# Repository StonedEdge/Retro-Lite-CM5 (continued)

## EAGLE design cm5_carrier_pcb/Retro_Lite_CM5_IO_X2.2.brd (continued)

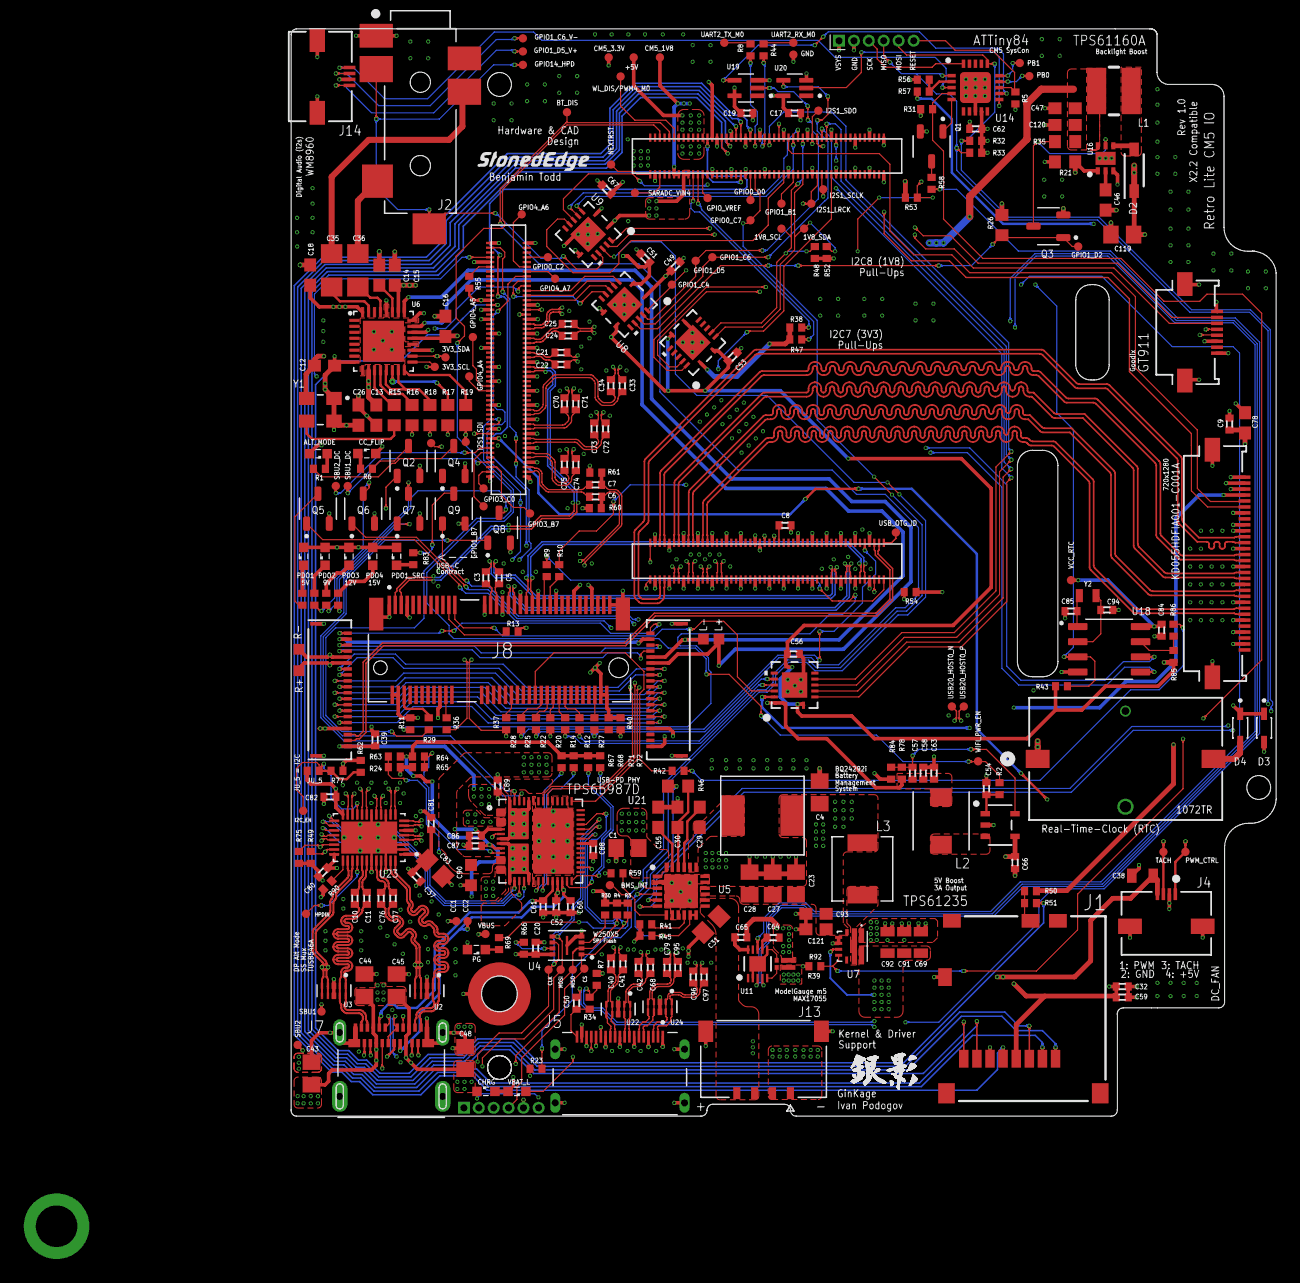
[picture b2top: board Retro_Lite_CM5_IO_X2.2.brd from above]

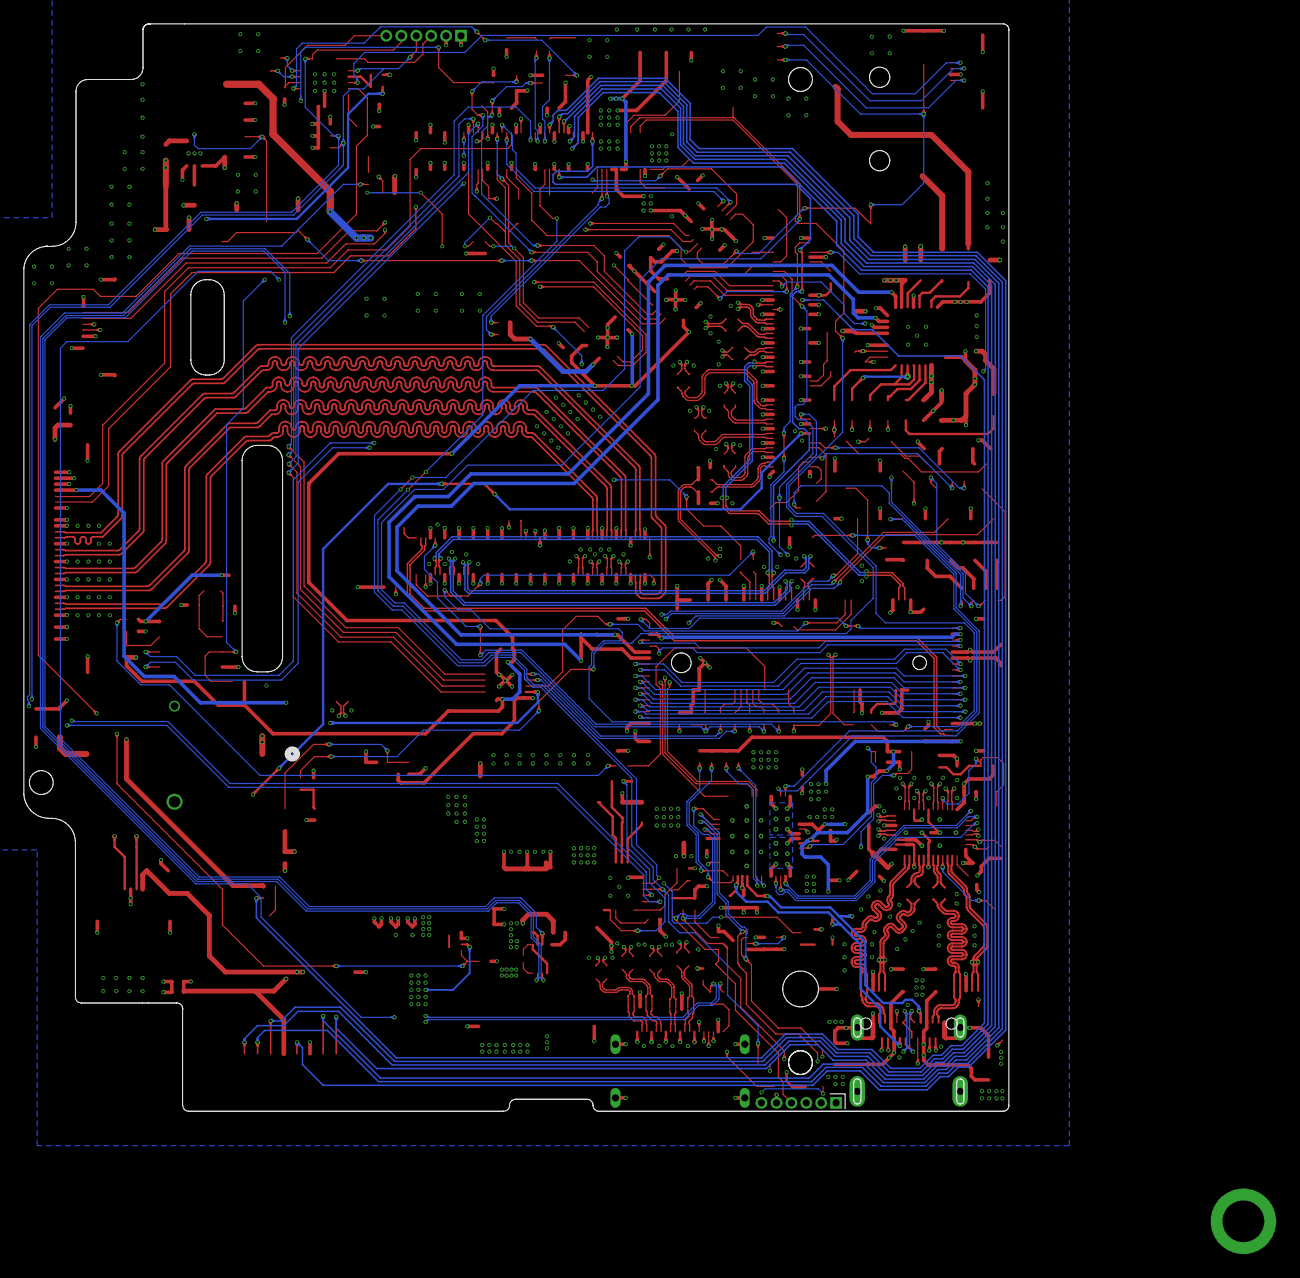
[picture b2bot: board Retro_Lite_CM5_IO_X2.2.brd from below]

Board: 6 copper layers, 82.7 x 91.3 mm, 318 parts (2 on the bottom side), 286 nets.

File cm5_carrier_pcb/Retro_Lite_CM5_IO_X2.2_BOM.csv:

Qty,Value,Device,Package,Parts,Description
6,N/A,LEDSML0603,SML0603,"PDO1, PDO1_SRC, PDO2, PDO3, PDO4, SSMX_DP_ACTIVE, SSMX_FLIP_ACTIVE",BLUE_LED_GENERIC
1,N/A,LEDSML0603,SML0603,CHRG,WHITE_LED_GENERIC
1,N/A,LEDSML0603,SML0603,VBAT_L,RED_LED_GENERIC
5,0R,R-EU_R0402,R0402,"JU_5, R13, R34, R36, R42",Resistor
1,0.047µF,C-EUC0603,C0603,C29,Capacitor
1,0.1uF,C-EUC0402,C0402,C20,Capacitor
6,0.1uF,C-EUC0402-YVELTAL,C0402,"C17, C19, C39, C54, C62, C65",Capacitor
4,0.1uF,C-EUC0603,C0603,"C12, C13, C18, C26",Capacitor
1,0.47uF,C-EUC0402-YVELTAL,C0402,C64,Capacitor
2,0R,R-EU_R0402,R0402,"R51, R54",Resistor
1,1.0uF,1.0UF-0603-16V-10%,C0603,C93,Capacitor
5,1.8k,R-EU_R0402,R0402,"R38, R47, R48, R52, R53",Resistor
2,100K,R-EU_R0402,R0402,"R60, R61",Resistor
3,100R,R-EU_R0402,R0402,"R8, R44, R55",Resistor
1,100k,R-EU_R0402,R0402,R50,Resistor
3,100k 1%,R-EU_R0402,R0402,"R24, R64, R65",Resistor
18,100nF,C-EUC0402,C0402,"C6, C7, C21, C22, C24, C25, C33, C34, C37, C70, C71, C72, C73, C74, C75, C80, C81, C82",Capacitor
12,100nF,C-EUC0402-YVELTAL,C0402,"C3, C5, C9, C32, C49, C51, C53, C56, C63, C67, C84, C94",Capacitor
1,100pF,C-EUC0402-YVELTAL,C0402,C57,Capacitor
2,100uF,C-EUC1206,C1206,"C35, C36",Capacitor
1,105450-0101,105450-0101,MOLEX_105450-0101,J7,USB-C Connector
1,1072TR,1072TR,CONN_1072TR_KEY,J11,Coin Cell Connector
5,10K,R-EU_R0402,R0402,"R11, R27, R40, R62, R90",Resistor
5,10R,R-EU_R0603,R0603,"R15, R16, R17, R18, R19",Resistor
12,10k,R-EU_R0402,R0402,"R1, R2, R6, R31, R56, R77, R79, R80, R81, R82, R83, R85",Resistor
2,10k,R-EU_R0603,R0603,"R26, R35",Resistor
1,10k 1%,R-EU_R0402,R0402,R63,Resistor
1,10kΩ,R-EU_R0402,R0402,R45,Resistor
1,10kΩ,R-EU_R0603,R0603,R46,Resistor
4,10nF,C-EUC0805,C0805,"C43, C44, C45, C48",Capacitor
1,10uF,1.0UF-0603-16V-10%,C0603,C121,Capacitor
1,10uF,1.0UF-0805-25V-(+80/-20%),C0805,C38,Capacitor
3,10uF,C-EUC0402,C0402,"C86, C87, C89",Capacitor
3,10uF,C-EUC0402-YVELTAL,C0402,"C58, C59, C66",Capacitor
1,10uF,C-EUC0603,C0603,C78,Capacitor
1,10uF,C-EUC0805,C0805,C83,Capacitor
5,10µF,C-EUC0805,C0805,"C4, C23, C27, C28, C31",Capacitor
1,12pF,C-EUC0402-YVELTAL,C0402,C85,Capacitor
1,1M,R-EU_R0402,R0402,R92,Resistor
2,1uF,C-EUC0402,C0402,"C8, C50",Capacitor
2,1uF,C-EUC0603,C0603,"C30, C55",Capacitor
1,1uH,SPM5020T-1R0M,IND_SPM5020T-1R0M,L3,Inductor
2,1µF,C-EUC0603,C0603,"C47, C120",Capacitor
1,1µF,C-EUC0805,C0805,C1,Capacitor
2,2.2k,R-EU_R0402,R0402,"R23, R58",Resistor
1,2.2uH,AMDLA4530S-2R2MT,IND_AMDLA4530S-2R2MT,L2,Inductor
12,220nF,C-EUC0402,C0402,"C10, C11, C40, C41, C42, C68, C76, C77, C79, C95, C96, C97",Capacitor
1,220nF,C-EUC0603,C0603,C46,Capacitor
2,220pF,C-EUC0402,C0402,"C60, C61",Capacitor
11,22R,R-EU_R0402,R0402,"R9, R10, R12, R14, R20, R22, R25, R28, R29, R37, R86",Resistor
3,22uF,1.0UF-0805-25V-10%,805,"C69, C91, C92",Capacitor
1,22uF,C-EUC0402,C0402,C52,Capacitor
1,22µH,VLCF4020T-220MR56,VLCF4020_1,L1,Inductor
1,232k,R-EU_R0402,R0402,R78,Resistor
1,261Ω,R-EU_R0402,R0402,R41,Resistor
1,27.4k,R-EU_R0402,R0402,R57,Resistor
2,2M,R-EU_R0402,R0402,"R49, R75",Resistor
4,3.3k,R-EU_R0402,R0402,"R3, R4, R30, R66",Resistor
7,4.7k,R-EU_R0402,R0402,"R5, R32, R33, R67, R68, R71, R72",Resistor
1,4.7uF,C-EUC0402,C0402,C88,Capacitor
3,4.7uF,C-EUC0603,C0603,"C14, C15, C16",Capacitor
1,4.7µF 50v,C-EUC0805,C0805,C119,Capacitor
1,47K,R-EU_R0402,R0402,R7,Resistor
1,47k,R-EU_R0402,R0402,R43,Resistor
1,47uF,C-EUC0603,C0603,C90,Capacitor
1,5025700893,5025700893,MOLEX_5025700893,J1,SD Card Connector
2,5034802000,5034802000,CON_5034802000_MOL,"J6, J12",Controller Board Connector
1,5040500491,5040500491,MOLEX_5040500491,J13,Battery Connector
2,5051100492,5051100492,CON_5051100492_MOL,"J4, J14",Fan/Volume/Power Connector
1,5051100892,5051100892,CON_5051100892_MOL,J10,CTP Connector
1,5051103091,5051103091,CON_5051103091_MOL,J9,MIPI Panel Connector
1,51k,R-EU_R0402,R0402,R84,Resistor
1,5Ω,R-EU_R0603,R0603,R21,Resistor
1,685119136923,685119136923,WURTH_685119136923,J5,HDMI Mini Connector
9,AO3400A,AO3400A,SOT95P280X125-3N,"Q1, Q2, Q3, Q4, Q5, Q6, Q7, Q8, Q9",Trans MOSFET N-CH 30V 5.7A 3-Pin SOT-23
1,ASPI-0630HI,ASPI-0630HI,ASPI-0630HI,L6,Inductor
2,B5819WS-TP,B5819WS-TP,SOD2512X115N,"D3, D4",Diode 40 V 1A Surface Mount SOD-323
1,BQ24292I,BQ24292I,QFN50P400X400X100-25N,U5,BQ24292i Charger IC Lithium Ion/Polymer 24-VQFN (4x4)
3,DF40C-100DS-0.4V(51),DF40C-100DS-0.4V(51),HRS_DF40C-100DS-0.4V(51),"CONNECTOR1, CONNECTOR2, CONNECTOR3",DF40 Series 100 Position Dual Row 0.4 mm Pitch Surface Mount Vertical Receptacle (Mezzanines)
1,ECS-.327-12.5-12R-TR,ECS-.327-12.5-12R-TR,XTAL_ECS-.327-12.5-12R-TR,Y2,SMD Crystal
1,ECS-3225MV-240-BN-TR,ECS-3225MV-240-BN-TR,OSC_ECS-2333-160-BN-TR,Y1,SMD Crystal
1,9774015243R (rev1) v1,9774015243R (rev1) v1,9774015243R (rev1) v1,H1,"Round Standoff Threaded M2x0.4 Steel 0.059"" (1.50mm)"
1,MAX17055ETB+T,MAX17055ETB+T,21-100013A_T102A2+1C_MXM,U11,Fuel Gauge
1,MBR0540T1G,MBR0540T1G,SOD3716X135N,D2,"0.5A 40V Schottky Rectifier, MBR0540T1G ON Semiconductor MBR0540T1G Schottky Diode, 0.5A, 40V, 2-Pin SOD-123"
1,MCU-ATTINY84A-MU(QFN20),MCU-ATTINY84A-MU(QFN20),QFN20G-0.5-4X4MM,U14,ATtiny84 Microcontroller
1,MDT320E01001,MDT320E01001,AMPHENOL_MDT320E01001,J8,"67 Position Female Connector M.2 (NGFF) Mini Card Gold 0.020"" (0.50mm) Black - Board Lock, E-Keyed (WiFi)"
1,PS0306DRF7T0R01L,PS0306DRF7T0R01L,PS0306DRF7T0R01L,R39,"10 mOhms ±0.5% 0.5W, 1/2W Chip Resistor Wide 0603 (1608 Metric), 0306 Current Sense Metal Element"
1,SJ-43516-SMT,SJ-43516-SMT,CUI_SJ-43516-SMT,J2,Conn 3.5MM Audio Jack F 6 POS Solder RA SMD 6 Terminal 1 Port
2,SN74LVC1G17DCKR,SN74LVC1G17DCKR,SOT65P210X110-5N,"U19, U20","Buffer, Non-Inverting 1 Element 1 Bit per Element Push-Pull Output SC-70-5"
1,SY8089AAACSY8089AAAC_SGY-L,SY8089AAACSY8089AAAC_SGY-L,SY8089AAAC_SGY-L,U12,"SY8089 and SY8089A are high-efficiency, high frequency synchronous step-down DC-DC regulator IC capable of delivering up to 2A output current"
4,TPD4E05U06DQAR,TPD4E05U06DQAR,IC_TPD4E05U06DQAR,"U2, U3, U22, U24",14V Clamp 2.5A (8/20µs) Ipp Tvs Diode Surface Mount 10-USON (2.5x1)
1,TPS61160ADRVT,TPS61160ADRVT,SON65P200X200X80-7N,U16,White LED Driver with PWM Brightness Control in 2mm x 2mm Package. Up to 10 LEDs in Series
1,TPS61235PRWLT,TPS61235PRWLT,CONV_TPS61235PRWLT,U7,TPS6123x 8-A Valley Current Synchronous Boost Converters with Constant Current Output Feature 9-VQFN-HR -40 to 85 Check availability
1,TPS65987DDHRSHR,TPS65987DDHRSHR,IC_TPS65987DDHRSHR,U21,USB Type-C™ and USB PD Controller With Integrated Power Switches 56-VQFN -40 to 85 Check availability
1,HYM8563TS,HYM8563TS,HYM8563TS,U18,HYM8563 CMOS RTC IC
1,TUSB546-DCIRNQT,TUSB546-DCIRNQT,QFN40P400X600X80-41N,U23,"Buffer, ReDriver 2 Channel 8.1Gbps 40-WQFN (4x6) "
4,UM3204QQFN14_3.5X3.5_UM3204_USC-L,UM3204QQFN14_3.5X3.5_UM3204_USC-L,QFN14_3.5X3.5_UM3204_USC-L,"U8, U9, U10, U13",Bidirectional Voltage-Level Translators
1,W25X05CLUXIGTR,W25X05CLUXIGTR,PSON50P300X200X60-9N,U4,SPI Flash Module
1,WM8960,WM8960,QFN50P500X500X100-33N,U6,Audio Amplifier

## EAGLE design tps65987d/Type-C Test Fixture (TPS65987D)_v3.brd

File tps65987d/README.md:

# TPS65987D Test Board v3

## What is this folder? 
This folder contains the test fixture schematic and board files (EAGLE) designed to test the functionality of the TPS65987D PD controller and TUSB546A superspeed mux, as well as other features that will be included on the main carrier board for the final build. Feel free to use it as a reference design for a USB-C DRP application in your designs. 
It also contains the project file that can be used to edit specific parameters in the TPS65987x GUI Application Tool, depending on your required use case. I used an RP2040 to flash the binary to the SPI module & final binary to be used in the CM5 will be uploaded when ready. 

## Purpose of PCB
To provide an environment to test out the TPS6598x GUI Application Tool, change parameters and flash a binary for a USB-C DRP application. The current CM5 is programmed with the parameters found in the .pjt file here. You can use this tool if you want to play around with it or change certain parameters to suit your specific application: https://www.ti.com/tool/TPS6598X-CONFIG

The flash module is an W25X05 and communicates with the PD device over the SPI bus. It loads this flash either via 3V3 power or dead battery mode via VBUS power. You can also program the TPS65987D (the USB-PD controller) via the I2C bus. 

The bottom USB-C connector is for plugging in sink/source device to charge the battery or power a USB device (like a keyboard, mouse or thumb drive). This will be the port on the final handheld itself. 

The top two USB-C ports are for high speed data buses, namely DisplayPort & USB 3.1.

The ATtiny is connected to the button, which is used to control power, sleep & regulator enable. We use this to safely tell the CM5 to shutdown before the enable pin is driven low. The ATtiny is also connected to the BQ24292i over I2C & sets the specific registers required for monitoring the battery - charging current, termination current, and other parameters like charge cutoff voltage. 

Flash the SPI module via the command line, for example, using serprog. 
```flashrom -p serprog:dev=/dev/ttyACM0:115200,spispeed=12M -c W25X05 -w .bin```

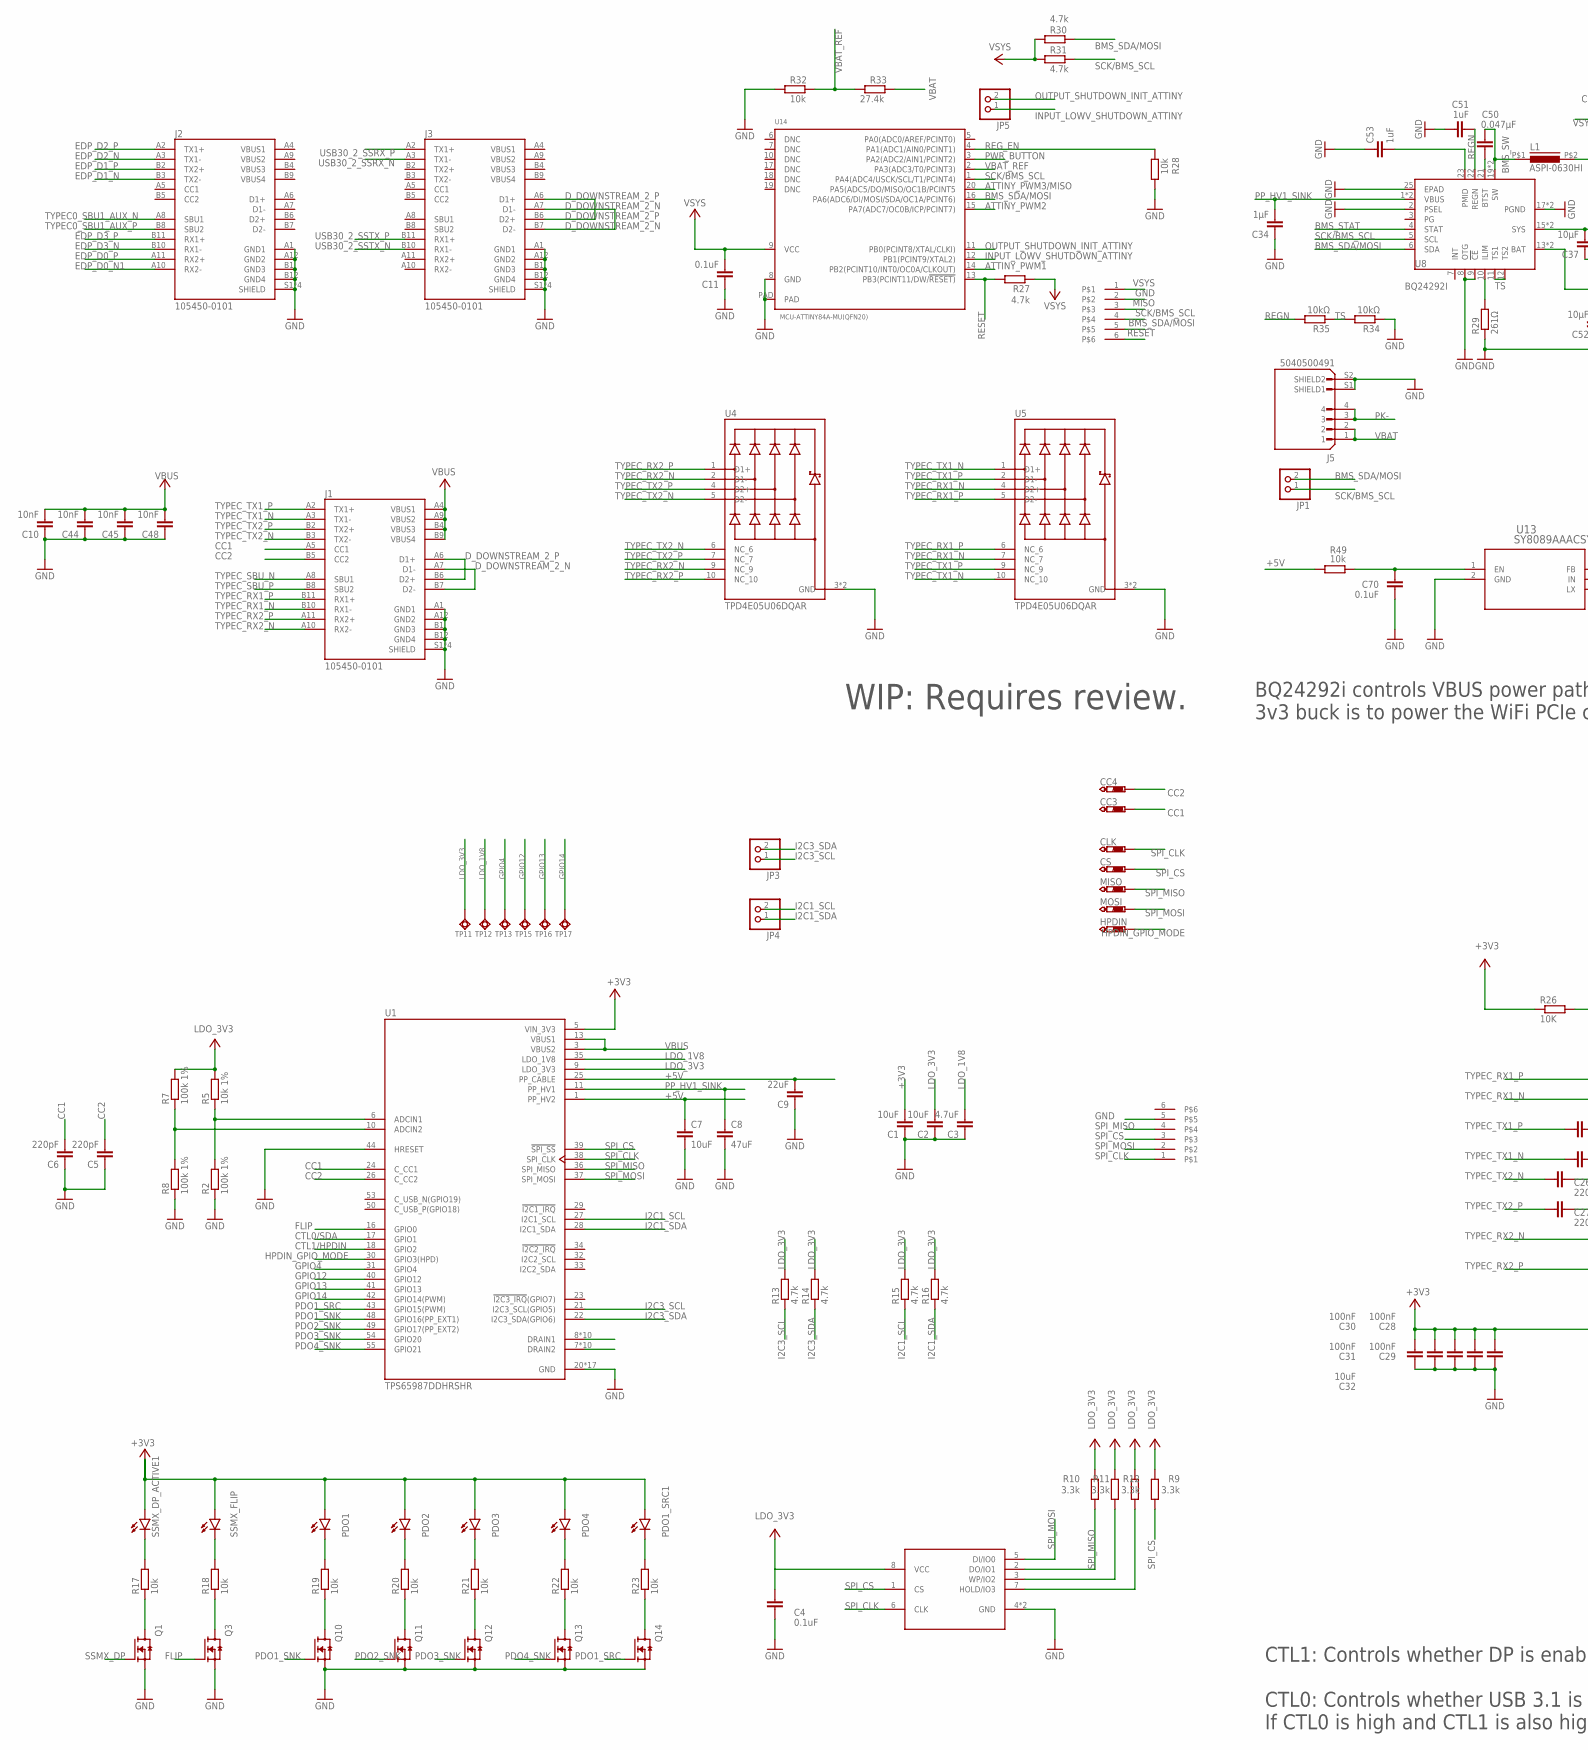
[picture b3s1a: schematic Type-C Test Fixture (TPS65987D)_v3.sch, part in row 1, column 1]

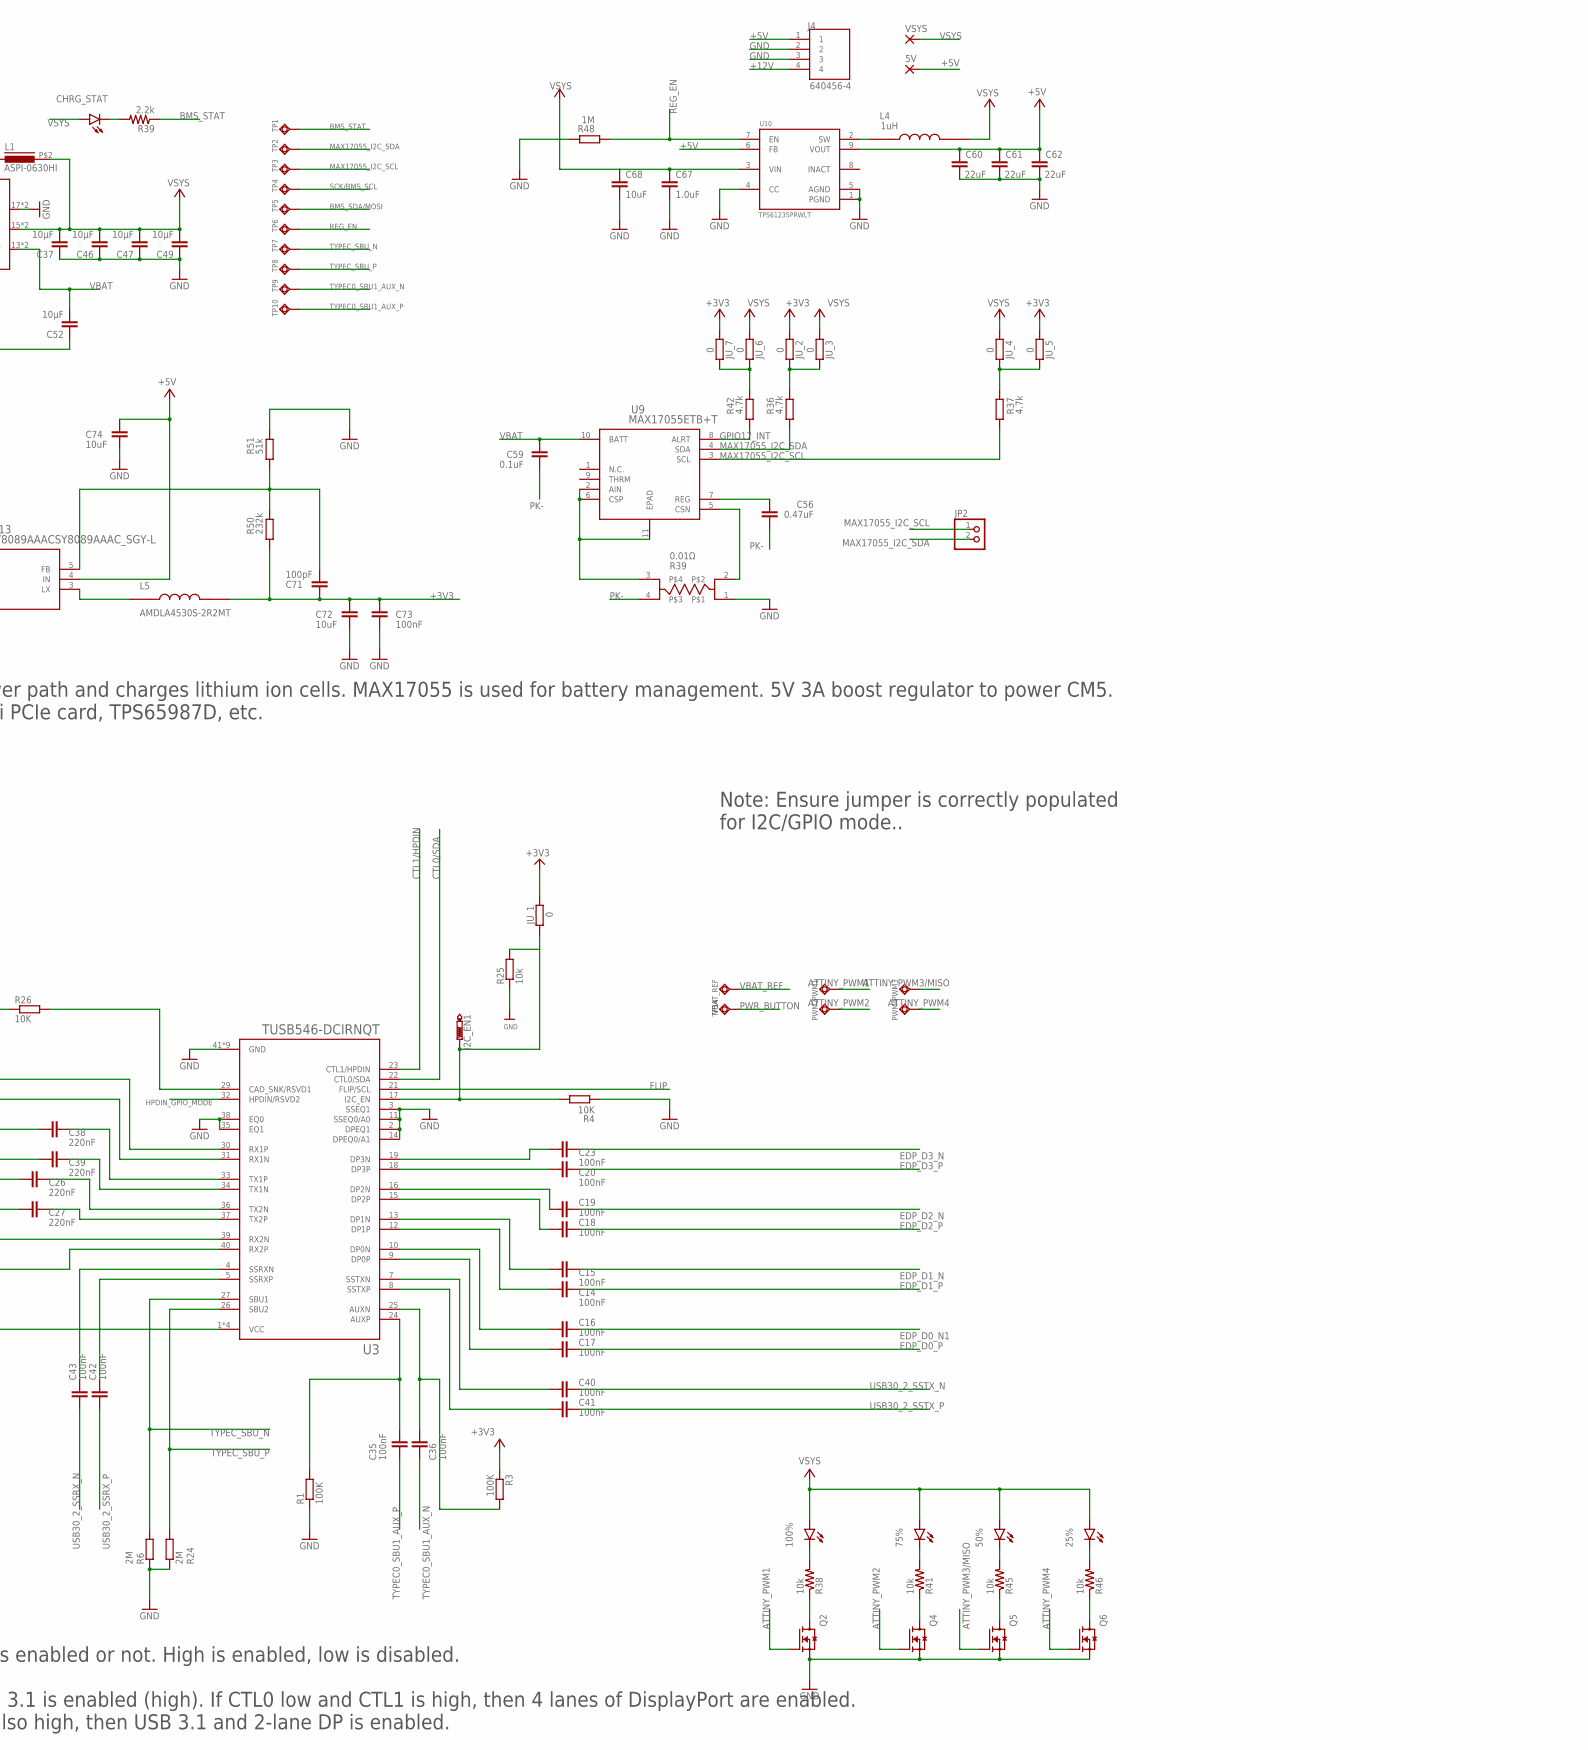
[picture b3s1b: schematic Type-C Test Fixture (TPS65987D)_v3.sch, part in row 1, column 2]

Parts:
5V: SMD5; SMD2,54-5,08
25%, 50%, 75%, 100%: LEDSML0603; SML0603
C1, C2, C7, C72, C74: 10uF; C0402
C3: 4.7uF; C0402
C4, C11, C59, C70: 0.1uF; C0402
C5, C6: 220pF; C0402
C8: 47uF; C0603
C9: 22uF; C0402
C10, C44, C45, C48: 10nF; C0805
C14, C15, C16, C17, C18, C19, C20, C23, C28, C29, C30, C31, C35, C36, C40, C41, C42, C43, C73: 100nF; C0402
C26, C27, C38, C39: 220nF; C0402
C32: 10uF; C0805
C34: 1µF; C0805
C37, C46, C47, C49, C52: 10µF; C0805
C50: 0.047µF; C0603
C51, C53: 1uF; C0603
C56: 0.47uF; C0402
C60, C61, C62: 22uF; 0805
C67: 1.0uF; 0603
C68: 10uF; 0603
C71: 100pF; C0402
CC3, CC4: PTR1TP07R; TP07R
CHRG_STAT: LEDSML0603; SML0603
CLK: PTR1TP07R; TP07R
CS: PTR1TP07R; TP07R
HPDIN: PTR1TP07R; TP07R
I2C_EN1: PTR1TP07R; TP07R
J1, J2, J3: 105450-0101; MOLEX_105450-0101
J4: 640456-4; TE_640456-4
J5: 5040500491; MOLEX_5040500491
JP1, JP2, JP3, JP4, JP5: PINHD-1X2; 1X02
JU_1, JU_2, JU_3, JU_4, JU_5, JU_6, JU_7: 0; R0402
L1: ASPI-0630HI
L4: 1uH; IND_SPM5020T-1R0M
L5: AMDLA4530S-2R2MT; IND_AMDLA4530S-2R2MT
MISO: PTR1TP07R; TP07R
MOSI: PTR1TP07R; TP07R
PDO1, PDO1_SRC1, PDO2, PDO3, PDO4: LEDSML0603; SML0603
PWM1, PWM2, PWM3, PWM4: TPSQTP07R; TP07R
Q1, Q2, Q3, Q4, Q5, Q6, Q10, Q11, Q12, Q13, Q14: AO3400A; SOT95P280X125-3N
R1, R3: 100K; R0402
R2, R7, R8: 100k 1%; R0402
R4, R26: 10K; R0402
R5: 10k 1%; R0402
R6, R24: 2M; R0402
R9, R10, R11, R12: 3.3k; R0402
R13, R14, R15, R16, R27, R30, R31, R36, R37, R42: 4.7k; R0402
R17, R18, R19, R20, R21, R22, R23, R25, R28, R32, R49: 10k; R0402
R29: 261Ω; R0402
R33: 27.4k; R0402
R34: 10kΩ; R0402
R35: 10kΩ; R0603
R38, R41, R45, R46: 10k; R0201
R39: 2.2k; R0201
R40: PS0306DRF7T0R01L
R48: 1M; R0402
R50: 232k; R0402
R51: 51k; R0402
SSMX_DP_ACTIVE1: LEDSML0603; SML0603
SSMX_FLIP_ACTIVE1: SSMX_FLIP; SML0603
TP1, TP2, TP3, TP4, TP5, TP6, TP7, TP8, TP9, TP10, TP11, TP12, TP13, TP14, TP15, TP16, TP17: TPSQTP07R; TP07R
U1: TPS65987DDHRSHR; IC_TPS65987DDHRSHR
U2: W25X05CLUXIGTR; PSON50P300X200X60-9N
U3: TUSB546-DCIRNQT; QFN40P400X600X80-41N
U4, U5: TPD4E05U06DQAR; IC_TPD4E05U06DQAR
U8: BQ24292I; QFN50P400X400X100-25N
U9: MAX17055ETB+T; 21-100013A_T102A2+1C_MXM
U10: TPS61235PRWLT; CONV_TPS61235PRWLT
U13: SY8089AAACSY8089AAAC_SGY-L; SY8089AAAC_SGY-L
U14: MCU-ATTINY84A-MU(QFN20); QFN20G-0.5-4X4MM
U$3, U$5: 6PINEADER; 1MM_PIC-PROGRAMING_HEADER
VBAT_REF: TPSQTP07R; TP07R
VSYS: SMD5; SMD2,54-5,08

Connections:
+3V3: C1.2, C28.2, C29.2, C30.2, C31.2, C32.2, C71.1, C72.1, C73.1, JU_1.2, JU_2.1, JU_5.1, JU_7.1, L5.2, PDO1.A, PDO1_SRC1.A, PDO2.A, PDO3.A, PDO4.A, R3.1, R26.1, R50.2, SSMX_DP_ACTIVE1.A, SSMX_FLIP_ACTIVE1.A, U1.5 (VIN_3V3), U3.1 (VCC), U3.6 (VCC), U3.20 (VCC), U3.28 (VCC)
+5V: 5V.1, C7.1, C9.2, C60.1, C61.1, C62.1, C74.1, J4.1, R49.2, U1.1 (PP_HV2), U1.25 (PP_CABLE), U10.6 (FB), U10.9 (VOUT), U13.4 (IN)
+12V: J4.4
ATTINY_PWM1: PWM1.TP, Q2.1 (G), U14.14 (PB2(PCINT10/INT0/OC0A/CLKOUT))
ATTINY_PWM2: PWM2.TP, Q4.1 (G), U14.15 (PA7(ADC7/OC0B/ICP/PCINT7))
ATTINY_PWM3/MISO: PWM3.TP, Q5.1 (G), U14.20 (PA5(ADC5/DO/MISO/OC1B/PCINT5)
ATTINY_PWM4: PWM4.TP, Q6.1 (G)
BMS_SDA/MOSI: JP1.2, R30.2, TP5.TP, U8.6 (SDA), U14.16 (PA6(ADC6/DI/MOSI/SDA/OC1A/PCINT6)), U$5.5
BMS_STAT: R39.1, TP1.TP, U8.4 (STAT)
BMS_SW: C50.1, L1.P$1 (1), U8.19 (SW), U8.20 (SW)
CC1: C6.2, CC3.TP, J1.A5 (CC1), U1.24 (C_CC1)
CC2: C5.2, CC4.TP, J1.B5 (CC2), U1.26 (C_CC2)
CTL0/SDA: U1.17 (GPIO1), U3.22 (CTL0/SDA)
CTL1/HPDIN: U1.18 (GPIO2), U3.23 (CTL1/HPDIN)
D_DOWNSTREAM_2_N: J1.A7 (D1-), J1.B7 (D2-), J3.A7 (D1-), J3.B7 (D2-)
D_DOWNSTREAM_2_P: J1.A6 (D1+), J1.B6 (D2+), J3.A6 (D1+), J3.B6 (D2+)
EDP_D0_N1: C16.1, C16.2, J2.A10 (RX2-), U3.10 (DP0N)
EDP_D0_P: C17.1, C17.2, J2.A11 (RX2+), U3.9 (DP0P)
EDP_D1_N: C15.1, C15.2, J2.B3 (TX2-), U3.13 (DP1N)
EDP_D1_P: C14.1, C14.2, J2.B2 (TX2+), U3.12 (DP1P)
EDP_D2_N: C19.1, C19.2, J2.A3 (TX1-), U3.16 (DP2N)
EDP_D2_P: C18.1, C18.2, J2.A2 (TX1+), U3.15 (DP2P)
EDP_D3_N: C23.1, C23.2, J2.B10 (RX1-), U3.19 (DP3N)
EDP_D3_P: C20.1, C20.2, J2.B11 (RX1+), U3.18 (DP3P)
FLIP: Q3.1 (G), U1.16 (GPIO0), U3.21 (FLIP/SCL)
GND: C1.1, C2.1, C3.1, C4.1, C5.1, C6.1, C7.2, C8.2, C9.1, C10.1, C11.1, C28.1, C29.1, C30.1, C31.1, C32.1, C34.1, C37.1, C44.1, C45.1, C46.1, C47.1, C48.1, C49.1, C51.1, C52.1, C53.1, C60.2, C61.2, C62.2, C67.2, C68.2, C70.2, C72.2, C73.2, C74.2, J1.A1 (GND1), J1.A12 (GND2), J1.B1 (GND3), J1.B12 (GND4), J1.S1 (SHIELD), J1.S2 (SHIELD), J1.S3 (SHIELD), J1.S4 (SHIELD), J2.A1 (GND1), J2.A12 (GND2), J2.B1 (GND3), J2.B12 (GND4), J2.S1 (SHIELD), J2.S2 (SHIELD), J2.S3 (SHIELD), J2.S4 (SHIELD), J3.A1 (GND1), J3.A12 (GND2), J3.B1 (GND3), J3.B12 (GND4), J3.S1 (SHIELD), J3.S2 (SHIELD), J3.S3 (SHIELD), J3.S4 (SHIELD), J4.2, J4.3, J5.S1 (SHIELD1), J5.S2 (SHIELD2), Q1.2 (S), Q2.2 (S), Q3.2 (S), Q4.2 (S), Q5.2 (S), Q6.2 (S), Q10.2 (S), Q11.2 (S), Q12.2 (S), Q13.2 (S), Q14.2 (S), R1.1, R2.1, R4.1, R6.1, R8.1, R24.1, R25.1, R28.1, R29.1, R32.1, R34.1, R40.1, R48.1, R51.1, U1.20 (GND), U1.44 (HRESET), U1.45 (GND), U1.46 (GND), U1.47 (GND), U1.51 (GND), U1.59 (GND), U1.59_1 (GND), U1.59_2 (GND), U1.59_3 (GND), U1.59_4 (GND), U1.59_5 (GND), U1.59_6 (GND), U1.59_7 (GND), U1.59_8 (GND), U1.59_9 (GND), U1.59_10 (GND), U1.59_11 (GND), U2.4 (GND), U2.9 (GND), U3.2 (DPEQ1), U3.3 (SSEQ1), U3.11 (SSEQ0/A0), U3.14 (DPEQ0/A1), U3.35 (EQ1), U3.38 (EQ0), U3.41 (GND), U3.42 (GND), U3.43 (GND), U3.44 (GND), U3.45 (GND), U3.46 (GND), U3.47 (GND), U3.48 (GND), U3.49 (GND), U4.3 (GND), U4.8 (GND), U5.3 (GND), U5.8 (GND), U8.2 (PSEL), U8.8 (OTG), U8.9 (!CE), U8.17 (PGND), U8.18 (PGND), U8.25 (EPAD), U10.1 (PGND), U10.4 (CC), U10.5 (AGND), U13.2 (GND), U14.8 (GND), U14.PAD, U$3.5, U$5.2
GPIO4: TP13.TP, U1.31 (GPIO4)
GPIO12: TP15.TP, U1.40 (GPIO12)
GPIO13: TP16.TP, U1.41 (GPIO13)
GPIO14: TP17.TP, U1.42 (GPIO14(PWM))
GPIO17_INT: R42.2, U9.8 (ALRT)
HPDIN_GPIO_MODE: HPDIN.TP, U1.30 (GPIO3(HPD)), U3.32 (HPDIN/RSVD2)
I2C1_SCL: JP4.2, R15.1, U1.27 (I2C1_SCL)
I2C1_SDA: JP4.1, R16.1, U1.28 (I2C1_SDA)
I2C3_SCL: JP3.1, R13.1, U1.21 (I2C3_SCL(GPIO5))
I2C3_SDA: JP3.2, R14.1, U1.22 (I2C3_SDA(GPIO6))
INPUT_LOWV_SHUTDOWN_ATTINY: JP5.1, U14.12 (PB1(PCINT9/XTAL2))
LDO_1V8: C3.2, TP12.TP, U1.35 (LDO_1V8)
LDO_3V3: C2.2, C4.2, R5.2, R7.2, R9.2, R10.2, R11.2, R12.2, R13.2, R14.2, R15.2, R16.2, TP11.TP, U1.9 (LDO_3V3), U2.8 (VCC)
MAX17055_I2C_SCL: JP2.1, R37.2, TP3.TP, U9.3 (SCL)
MAX17055_I2C_SDA: JP2.2, R36.2, TP2.TP, U9.4 (SDA)
MISO: U$5.3
unnamed: R2.2, R5.1, U1.6 (ADCIN1)
unnamed: I2C_EN1.TP, JU_1.1, R4.2, R25.2, U3.17 (I2C_EN)
unnamed: R7.1, R8.2, U1.10 (ADCIN2)
unnamed: R26.2, U3.29 (CAD_SNK/RSVD1)
unnamed: JU_6.2, JU_7.2, R42.1
unnamed: JU_2.2, JU_3.2, R36.1
unnamed: JU_4.2, JU_5.2, R37.1
unnamed: C50.2, U8.21 (BTST)
unnamed: U1.8 (DRAIN1), U1.15 (DRAIN1), U1.19 (DRAIN1), U1.58 (DRAIN1), U1.58_1 (DRAIN1), U1.58_2 (DRAIN1), U1.58_3 (DRAIN1), U1.58_4 (DRAIN1), U1.58_5 (DRAIN1), U1.58_6 (DRAIN1)
unnamed: R29.2, U8.10 (ILIM)
unnamed: C53.2, U8.23 (PMID)
unnamed: U1.7 (DRAIN2), U1.52 (DRAIN2), U1.56 (DRAIN2), U1.57 (DRAIN2), U1.57_1 (DRAIN2), U1.57_2 (DRAIN2), U1.57_3 (DRAIN2), U1.57_4 (DRAIN2), U1.57_5 (DRAIN2), U1.57_6 (DRAIN2)
unnamed: R11.1, U2.3 (WP/IO2)
unnamed: R12.1, U2.7 (HOLD/IO3)
unnamed: R17.2, SSMX_DP_ACTIVE1.C
unnamed: R18.2, SSMX_FLIP_ACTIVE1.C
unnamed: Q1.3 (D), R17.1
unnamed: L4.1, U10.2 (SW)
unnamed: Q3.3 (D), R18.1
unnamed: PDO1.C, R19.2
unnamed: PDO2.C, R20.2
unnamed: PDO3.C, R21.2
unnamed: PDO4.C, R22.2
unnamed: PDO1_SRC1.C, R23.2
unnamed: Q14.3 (D), R23.1
unnamed: Q13.3 (D), R22.1
unnamed: Q12.3 (D), R21.1
unnamed: Q10.3 (D), R19.1
unnamed: Q11.3 (D), R20.1
unnamed: C56.1, U9.7 (REG)
unnamed: R40.2, U9.5 (CSN)
unnamed: R40.3, U9.2 (AIN), U9.6 (CSP), U9.11 (EPAD)
unnamed: C70.1, R49.1, U13.1 (EN)
unnamed: L5.1, U13.3 (LX)
unnamed: C71.2, R50.1, R51.2, U13.5 (FB)
unnamed: C36.2, R3.2, U3.25 (AUXN)
unnamed: C35.2, R1.2, U3.24 (AUXP)
unnamed: CHRG_STAT.C, R39.2
unnamed: 100%.C, R38.2
unnamed: 75%.C, R41.2
unnamed: 50%.C, R45.2
unnamed: 25%.C, R46.2
unnamed: Q2.3 (D), R38.1
unnamed: Q4.3 (D), R41.1
unnamed: Q5.3 (D), R45.1
unnamed: Q6.3 (D), R46.1
OUTPUT_SHUTDOWN_INIT_ATTINY: JP5.2, U14.11 (PB0(PCINT8/XTAL/CLKI))
PDO1_SNK: Q10.1 (G), U1.48 (GPIO16(PP_EXT1))
PDO1_SRC: Q14.1 (G), U1.43 (GPIO15(PWM))
PDO2_SNK: Q11.1 (G), U1.49 (GPIO17(PP_EXT2))
PDO3_SNK: Q12.1 (G), U1.54 (GPIO20)
PDO4_SNK: Q13.1 (G), U1.55 (GPIO21)
PK-: C56.2, C59.2, J5.3, J5.4, R40.4
PP_HV1_SINK: C8.1, C34.2, U1.11 (PP_HV1), U8.1 (VBUS), U8.24 (VBUS)
PWR_BUTTON: TP14.TP, U14.3 (PA2(ADC2/AIN1/PCINT2))
REGN: C51.2, R35.2, U8.22 (REGN)
REG_EN: R28.2, R48.2, TP6.TP, U10.7 (EN), U14.4 (PA1(ADC1/AIN0/PCINT1))
RESET: R27.2, U14.13 (PB3(PCINT11/DW/!RESET)), U$5.6
SCK/BMS_SCL: JP1.1, R31.2, TP4.TP, U8.5 (SCL), U14.1 (PA4(ADC4/USCK/SCL/T1/PCINT4)), U$5.4
SPI_CLK: CLK.TP, U1.38 (SPI_CLK), U2.6 (CLK), U$3.1
SPI_CS: CS.TP, R9.1, U1.39 (!SPI_SS), U2.1 (CS), U$3.3
SPI_MISO: MISO.TP, R10.1, U1.36 (SPI_MISO), U2.2 (DO/IO1), U$3.4
SPI_MOSI: MOSI.TP, U1.37 (SPI_MOSI), U2.5 (DI/IO0), U$3.2
SSMX_DP: Q1.1 (G)
TS: R34.2, R35.1, U8.11 (TS1), U8.12 (TS2)
TYPEC0_SBU1_AUX_N: C36.1, J2.A8 (SBU1), TP9.TP
TYPEC0_SBU1_AUX_P: C35.1, J2.B8 (SBU2), TP10.TP
TYPEC_RX1_N: J1.B10 (RX1-), U3.31 (RX1N), U5.4 (D2+), U5.7 (NC_7)
TYPEC_RX1_P: J1.B11 (RX1+), U3.30 (RX1P), U5.5 (D2-), U5.6 (NC_6)
TYPEC_RX2_N: J1.A10 (RX2-), U3.39 (RX2N), U4.2 (D1-), U4.9 (NC_9)
TYPEC_RX2_P: J1.A11 (RX2+), U3.40 (RX2P), U4.1 (D1+), U4.10 (NC_10)
TYPEC_SBU_N: J1.A8 (SBU1), R6.2, TP7.TP, U3.27 (SBU1)
TYPEC_SBU_P: J1.B8 (SBU2), R24.2, TP8.TP, U3.26 (SBU2)
TYPEC_TX1_N: C39.1, C39.2, J1.A3 (TX1-), U3.34 (TX1N), U5.1 (D1+), U5.10 (NC_10)
TYPEC_TX1_P: C38.1, C38.2, J1.A2 (TX1+), U3.33 (TX1P), U5.2 (D1-), U5.9 (NC_9)
TYPEC_TX2_N: C26.1, C26.2, J1.B3 (TX2-), U3.36 (TX2N), U4.5 (D2-), U4.6 (NC_6)
TYPEC_TX2_P: C27.1, C27.2, J1.B2 (TX2+), U3.37 (TX2P), U4.4 (D2+), U4.7 (NC_7)
USB30_2_SSRX_N: C43.1, C43.2, J3.A3 (TX1-), U3.4 (SSRXN)
USB30_2_SSRX_P: C42.1, C42.2, J3.A2 (TX1+), U3.5 (SSRXP)
USB30_2_SSTX_N: C40.1, C40.2, J3.B10 (RX1-), U3.7 (SSTXN)
USB30_2_SSTX_P: C41.1, C41.2, J3.B11 (RX1+), U3.8 (SSTXP)
VBAT: C52.2, C59.1, J5.1, J5.2, R33.2, U8.13 (BAT), U8.14 (BAT), U9.10 (BATT)
VBAT_REF: R32.2, R33.1, U14.2 (PA3(ADC3/T0/PCINT3)), VBAT_REF.TP
VBUS: C10.2, C44.2, C45.2, C48.2, J1.A4 (VBUS1), J1.A9 (VBUS2), J1.B4 (VBUS3), J1.B9 (VBUS4), U1.3 (VBUS2), U1.13 (VBUS1)
VSYS: 25%.A, 50%.A, 75%.A, 100%.A, C11.2, C37.2, C46.2, C47.2, C49.2, C67.1, C68.1, CHRG_STAT.A, JU_3.1, JU_4.1, JU_6.1, L1.P$2 (2), L4.2, R27.1, R30.1, R31.1, U8.15 (SYS), U8.16 (SYS), U10.3 (VIN), U14.9 (VCC), U$5.1, VSYS.1

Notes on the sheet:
CTL1: Controls whether DP is enabled or not. High is enabled, low is disabled. CTL0: Controls whether USB 3.1 is enabled (high). If CTL0 low and CTL1 is high, then 4 lanes of DisplayPort are enabled. If CTL0 is high and CTL1 is also high, then USB 3.1 and 2-lane DP is enabled.
Note: Ensure jumper is correctly populated for I2C/GPIO mode..
WIP: Requires review.
R39
0.01Ω
BQ24292i controls VBUS power path and charges lithium ion cells. MAX17055 is used for battery management. 5V 3A boost regulator to power CM5. 3v3 buck is to power the WiFi PCIe card, TPS65987D, etc.
